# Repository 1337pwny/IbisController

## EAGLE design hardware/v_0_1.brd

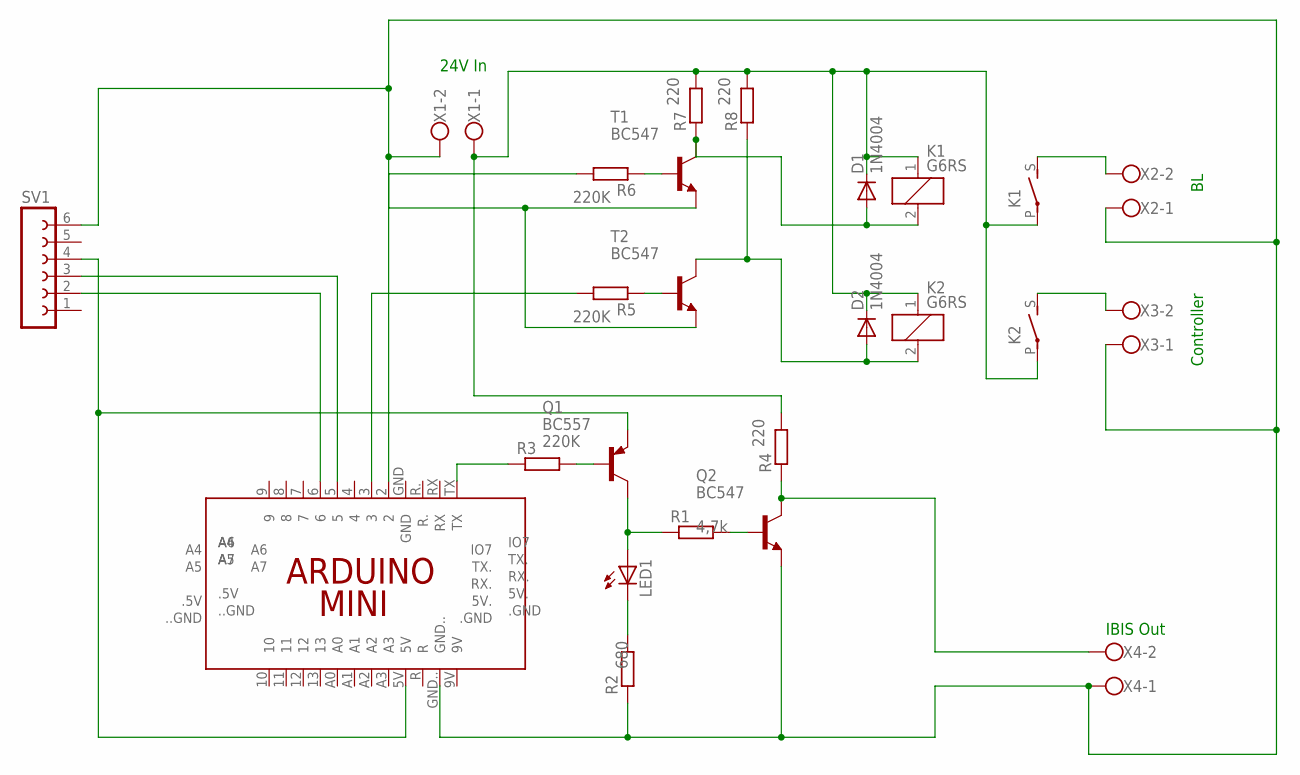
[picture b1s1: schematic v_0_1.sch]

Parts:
D1, D2: 1N4004; DO41-10
K1, K2: G6RS
LED1: LED5MM
PCB1: ARDUINO_MINI
Q1: BC557; TO92-EBC
Q2: BC547; TO92
R1, R2, R3, R4, R5, R6, R7, R8: R-EU_0207/10; 0207/10
SV1: FE06-1; FE06
T1, T2: BC547; TO92
X1, X2, X3, X4: W237-102

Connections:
unnamed: PCB1.GND.., Q2.1 (E), R2.1, SV1.6, T1.1 (E), T2.1 (E), X1.2, X2.1, X3.1, X4.1
unnamed: LED1.K (C), R2.2
unnamed: LED1.A, Q1.C, R1.1
unnamed: Q1.B, R3.2
unnamed: PCB1.TX, R3.1
unnamed: PCB1.5V, Q1.E, SV1.4
unnamed: Q2.3 (C), R4.1, X4.2
unnamed: Q2.2 (B), R1.2
unnamed: PCB1.2, R6.2
unnamed: PCB1.3, R5.2
unnamed: D1.A, K1.2, R7.1, T1.3 (C)
unnamed: D1.C, D2.C, K1.1, K1.P, K2.1, K2.P, R4.2, R7.2, R8.2, X1.1
unnamed: D2.A, K2.2, R8.1, T2.3 (C)
unnamed: K1.S, X2.2
unnamed: K2.S, X3.2
unnamed: PCB1.6, SV1.2
unnamed: R5.1, T2.2 (B)
unnamed: R6.1, T1.2 (B)
unnamed: PCB1.5, SV1.3

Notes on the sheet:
24V In
Controller
IBIS Out

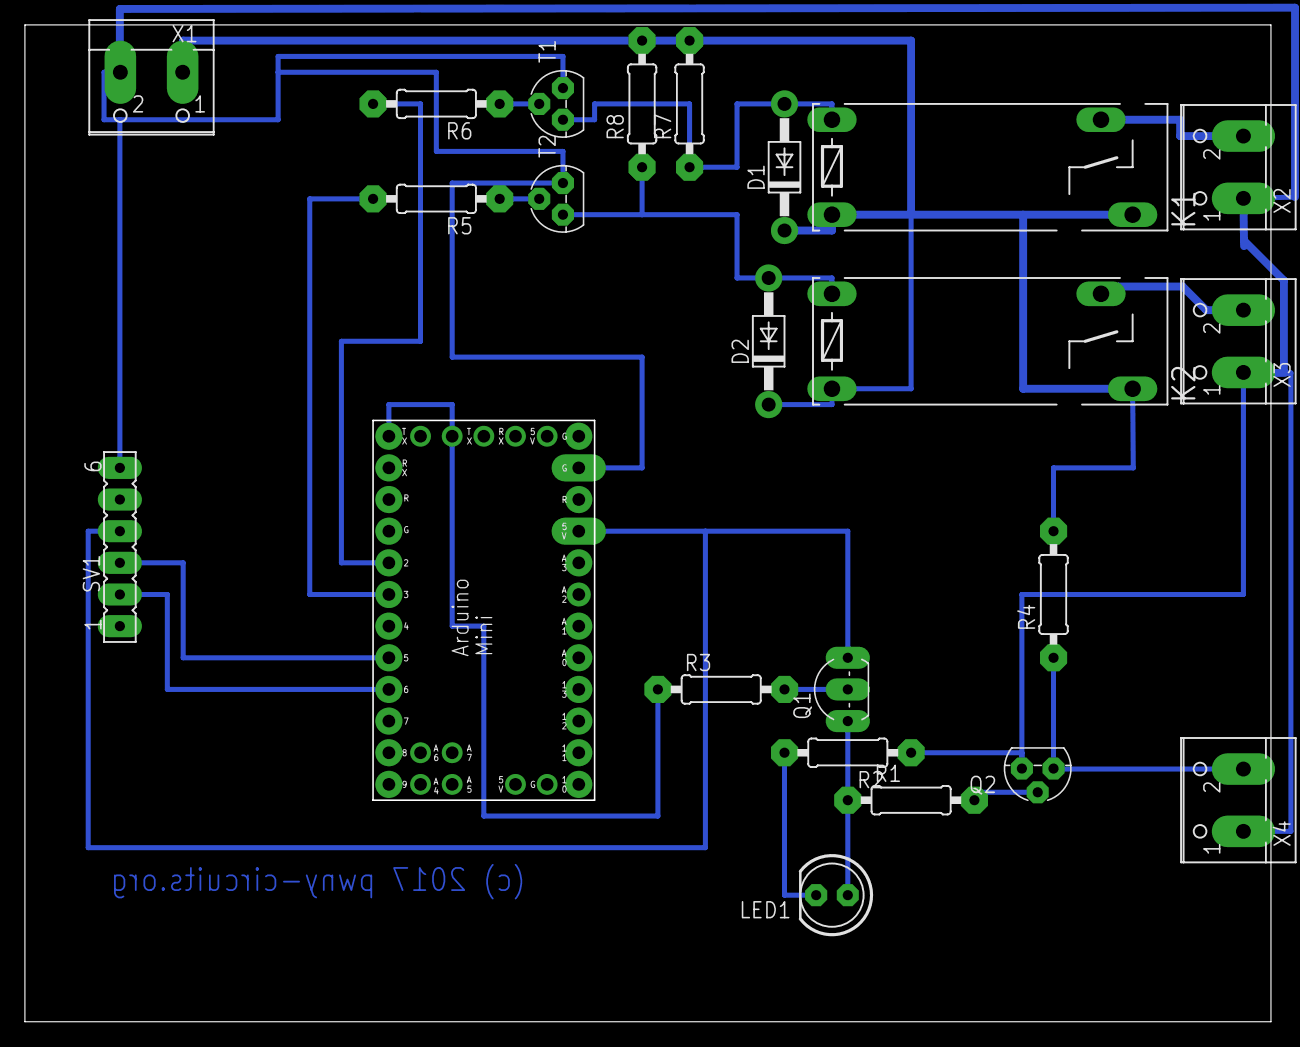
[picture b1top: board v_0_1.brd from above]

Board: 2 copper layers, 99.9 x 79.9 mm, 23 parts (0 on the bottom side), 19 nets.

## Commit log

2017-10-10 adds hardware layout

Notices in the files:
hardware/v_0_1.brd:
(c) 2017 pwny-circuits.org
